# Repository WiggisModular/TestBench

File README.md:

# TestBench

An Eurorack breadboard/perfboard module

## Clone it

`git clone https://github.com/WiggisModular/TestBench.git`

`git submodule init`

`git submodule update`

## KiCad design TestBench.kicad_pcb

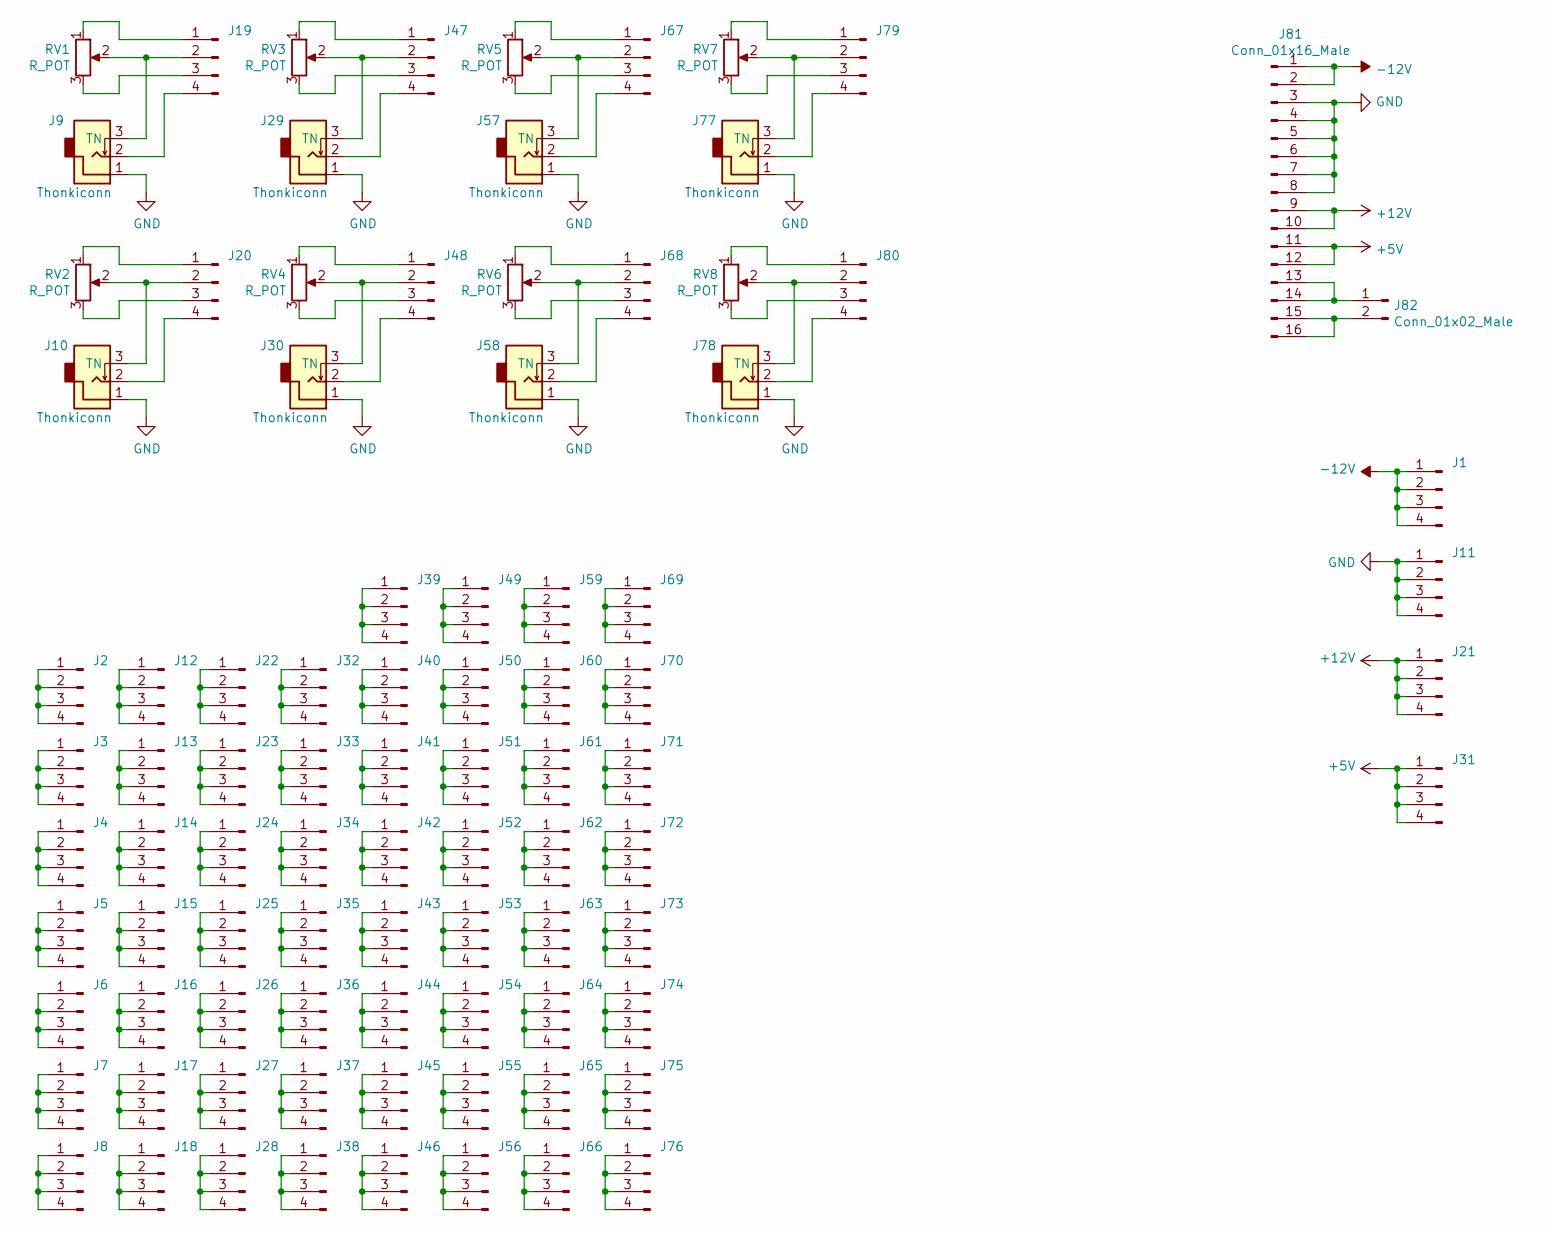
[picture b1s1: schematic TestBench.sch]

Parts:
J1, J2, J3, J4, J5, J6, J7, J8, J11, J12, J13, J14, J15, J16, J17, J18, J19, J20, J21, J22, J23, J24, J25, J26, J27, J28, J31, J32, J33, J34, J35, J36, J37, J38, J39, J40, J41, J42, J43, J44, J45, J46, J47, J48, J49, J50, J51, J52, J53, J54, J55, J56, J59, J60, J61, J62, J63, J64, J65, J66, J67, J68, J69, J70, J71, J72, J73, J74, J75, J76, J79, J80: Conn_01x04_Male; PinSocket_1x04_P2.54mm_Vertical
J9, J10, J29, J30, J57, J58, J77, J78: Thonkiconn
J81: Conn_01x16_Male; PinSocket_2x08_P2.54mm_Vertical
J82: Conn_01x02_Male; PinSocket_1x02_P2.54mm_Vertical
RV1, RV2, RV3, RV4, RV5, RV6, RV7, RV8: R_POT; Potentiometer_Alps_RK09K_Single_Vertical

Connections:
+5V: J31.1, J31.2, J31.3, J31.4, J81.11, J81.12
+12V: J21.1, J21.2, J21.3, J21.4, J81.9, J81.10
-12V: J1.1, J1.2, J1.3, J1.4, J81.1, J81.2
GND: J9.1, J10.1, J11.1, J11.2, J11.3, J11.4, J29.1, J30.1, J57.1, J58.1, J77.1, J78.1, J81.3, J81.4, J81.5, J81.6, J81.7, J81.8
unnamed: J2.1, J2.2, J2.3, J2.4
unnamed: J3.1, J3.2, J3.3, J3.4
unnamed: J4.1, J4.2, J4.3, J4.4
unnamed: J5.1, J5.2, J5.3, J5.4
unnamed: J6.1, J6.2, J6.3, J6.4
unnamed: J7.1, J7.2, J7.3, J7.4
unnamed: J8.1, J8.2, J8.3, J8.4
unnamed: J10.2, J20.4
unnamed: J10.3 (TN), J20.2, RV2.2
unnamed: J12.1, J12.2, J12.3, J12.4
unnamed: J13.1, J13.2, J13.3, J13.4
unnamed: J14.1, J14.2, J14.3, J14.4
unnamed: J15.1, J15.2, J15.3, J15.4
unnamed: J16.1, J16.2, J16.3, J16.4
unnamed: J17.1, J17.2, J17.3, J17.4
unnamed: J18.1, J18.2, J18.3, J18.4
unnamed: J19.1, RV1.1
unnamed: J9.3 (TN), J19.2, RV1.2
unnamed: J19.3, RV1.3
unnamed: J9.2, J19.4
unnamed: J20.1, RV2.1
unnamed: J20.3, RV2.3
unnamed: J22.1, J22.2, J22.3, J22.4
unnamed: J23.1, J23.2, J23.3, J23.4
unnamed: J24.1, J24.2, J24.3, J24.4
unnamed: J25.1, J25.2, J25.3, J25.4
unnamed: J26.1, J26.2, J26.3, J26.4
unnamed: J27.1, J27.2, J27.3, J27.4
unnamed: J28.1, J28.2, J28.3, J28.4
unnamed: J29.2, J47.4
unnamed: J29.3 (TN), J47.2, RV3.2
unnamed: J30.2, J48.4
unnamed: J30.3 (TN), J48.2, RV4.2
unnamed: J32.1, J32.2, J32.3, J32.4
unnamed: J33.1, J33.2, J33.3, J33.4
unnamed: J34.1, J34.2, J34.3, J34.4
unnamed: J35.1, J35.2, J35.3, J35.4
unnamed: J36.1, J36.2, J36.3, J36.4
unnamed: J37.1, J37.2, J37.3, J37.4
unnamed: J38.1, J38.2, J38.3, J38.4
unnamed: J39.1, J39.2, J39.3, J39.4
unnamed: J40.1, J40.2, J40.3, J40.4
unnamed: J41.1, J41.2, J41.3, J41.4
unnamed: J42.1, J42.2, J42.3, J42.4
unnamed: J43.1, J43.2, J43.3, J43.4
unnamed: J44.1, J44.2, J44.3, J44.4
unnamed: J45.1, J45.2, J45.3, J45.4
unnamed: J46.1, J46.2, J46.3, J46.4
unnamed: J47.1, RV3.1
unnamed: J47.3, RV3.3
unnamed: J48.1, RV4.1
unnamed: J48.3, RV4.3
unnamed: J49.1, J49.2, J49.3, J49.4
unnamed: J50.1, J50.2, J50.3, J50.4
unnamed: J51.1, J51.2, J51.3, J51.4
unnamed: J52.1, J52.2, J52.3, J52.4
unnamed: J53.1, J53.2, J53.3, J53.4
unnamed: J54.1, J54.2, J54.3, J54.4
unnamed: J55.1, J55.2, J55.3, J55.4
unnamed: J56.1, J56.2, J56.3, J56.4
unnamed: J57.2, J67.4
unnamed: J57.3 (TN), J67.2, RV5.2
unnamed: J58.2, J68.4
unnamed: J58.3 (TN), J68.2, RV6.2
unnamed: J59.1, J59.2, J59.3, J59.4
unnamed: J60.1, J60.2, J60.3, J60.4
unnamed: J61.1, J61.2, J61.3, J61.4
unnamed: J62.1, J62.2, J62.3, J62.4
unnamed: J63.1, J63.2, J63.3, J63.4
unnamed: J64.1, J64.2, J64.3, J64.4
unnamed: J65.1, J65.2, J65.3, J65.4
unnamed: J66.1, J66.2, J66.3, J66.4
unnamed: J67.1, RV5.1
unnamed: J67.3, RV5.3
unnamed: J68.1, RV6.1
unnamed: J68.3, RV6.3
unnamed: J69.1, J69.2, J69.3, J69.4
unnamed: J70.1, J70.2, J70.3, J70.4
unnamed: J71.1, J71.2, J71.3, J71.4
unnamed: J72.1, J72.2, J72.3, J72.4
unnamed: J73.1, J73.2, J73.3, J73.4
unnamed: J74.1, J74.2, J74.3, J74.4
unnamed: J75.1, J75.2, J75.3, J75.4
unnamed: J76.1, J76.2, J76.3, J76.4
unnamed: J77.2, J79.4
unnamed: J77.3 (TN), J79.2, RV7.2
unnamed: J78.2, J80.4
unnamed: J78.3 (TN), J80.2, RV8.2
unnamed: J79.1, RV7.1
unnamed: J79.3, RV7.3
unnamed: J80.1, RV8.1
unnamed: J80.3, RV8.3
unnamed: J81.13, J81.14, J82.1
unnamed: J81.15, J81.16, J82.2

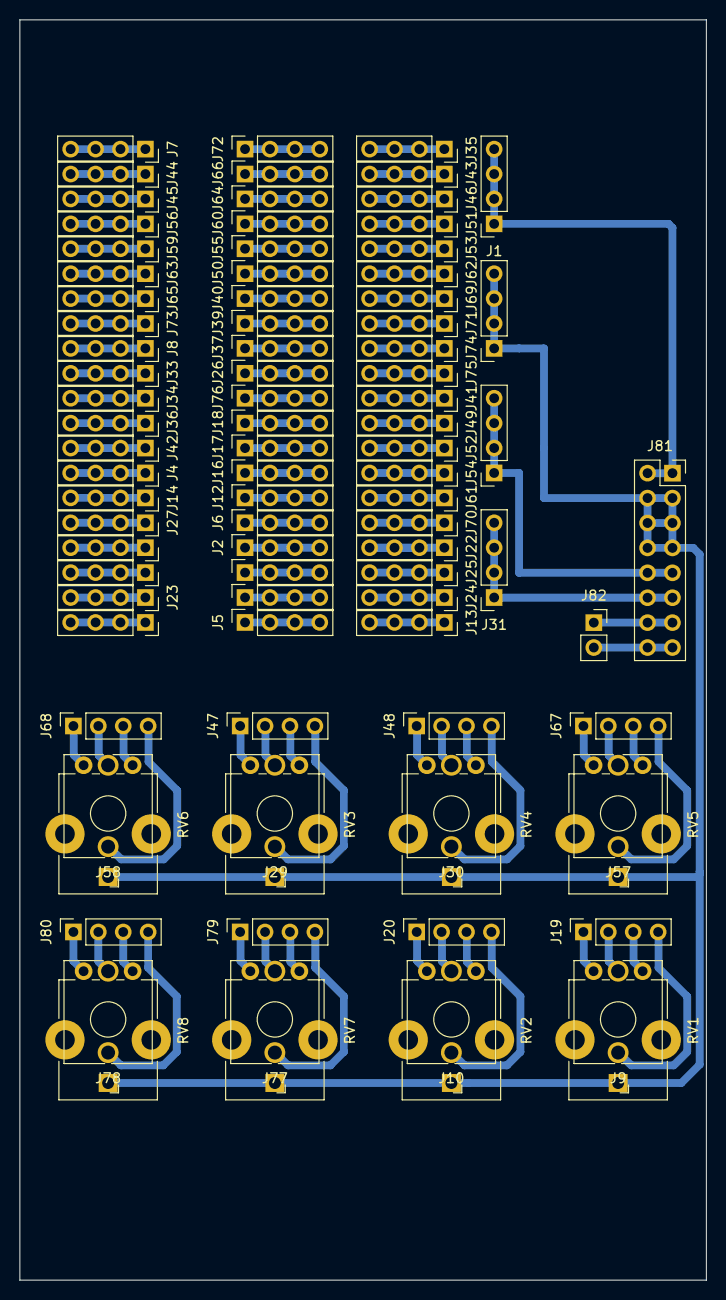
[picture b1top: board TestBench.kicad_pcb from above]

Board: 2 copper layers, 70.0 x 128.5 mm, 90 parts (0 on the bottom side), 98 nets.

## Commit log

2020-04-21 first Kicad_Eurorack submodule added
2020-04-21 cloning info added
2020-04-21 schematics and routing done
